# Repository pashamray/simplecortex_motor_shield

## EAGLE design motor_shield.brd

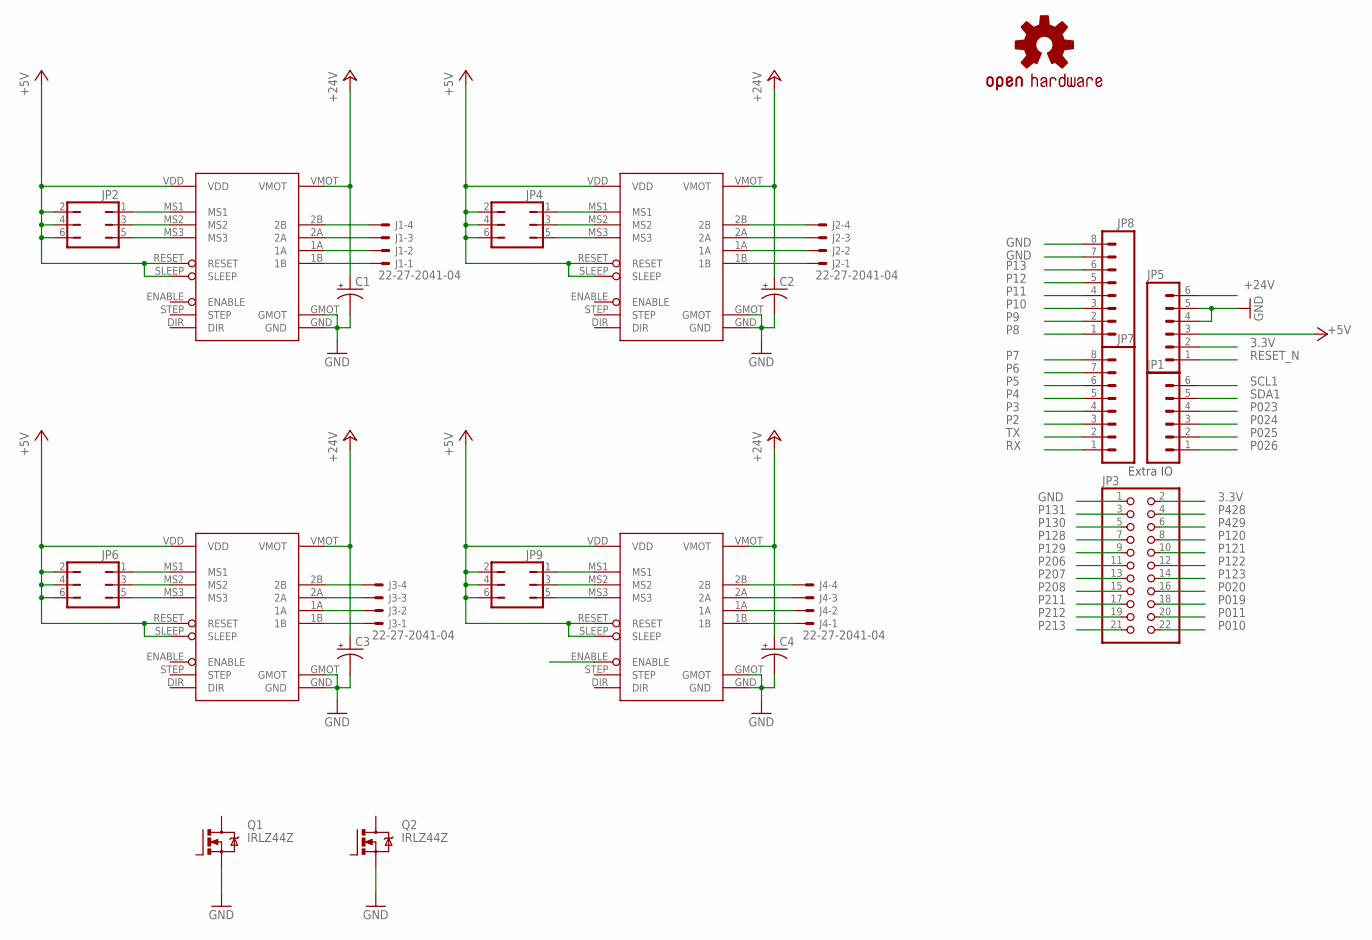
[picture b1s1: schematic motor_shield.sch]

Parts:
C1, C2, C3, C4: CAP_POLPTH1; CPOL-RADIAL-100UF-25V
J1, J2, J3, J4: 22-27-2041-04; 6410-04
JP1, JP5: M06SIP; 1X06
JP2, JP4, JP6, JP9: JP3Q
JP3: PINHD-2X11; 2X11
JP7, JP8: M08; 1X08
OPENHARDWARE: OSHW-LOGOL; OSHW-LOGO-L
Q1, Q2: IRLZ44Z; TO220BH
U$1, U$2, U$3, U$4: A4988

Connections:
3.3V: JP3.2, JP5.2
+5V: JP2.2, JP2.4, JP2.6, JP4.2, JP4.4, JP4.6, JP5.3, JP6.2, JP6.4, JP6.6, JP9.2, JP9.4, JP9.6, U$1.RESET, U$1.SLEEP, U$1.VDD, U$2.RESET, U$2.SLEEP, U$2.VDD, U$3.RESET, U$3.SLEEP, U$3.VDD, U$4.RESET, U$4.SLEEP, U$4.VDD
+24V: C1.1 (+), C2.1 (+), C3.1 (+), C4.1 (+), JP5.6, U$1.VMOT, U$2.VMOT, U$3.VMOT, U$4.VMOT
GND: C1.2 (-), C2.2 (-), C3.2 (-), C4.2 (-), JP3.1, JP5.4, JP5.5, JP8.7, JP8.8, Q1.S, Q2.S, U$1.GMOT, U$1.GND, U$2.GMOT, U$2.GND, U$3.GMOT, U$3.GND, U$4.GMOT, U$4.GND
unnamed: J1.4, U$1.2B
unnamed: J1.3, U$1.2A
unnamed: J1.2, U$1.1A
unnamed: J1.1, U$1.1B
unnamed: JP2.1, U$1.MS1
unnamed: JP2.3, U$1.MS2
unnamed: JP2.5, U$1.MS3
unnamed: J2.4, U$2.2B
unnamed: J2.3, U$2.2A
unnamed: J2.2, U$2.1A
unnamed: J2.1, U$2.1B
unnamed: JP6.1, U$3.MS1
unnamed: JP6.3, U$3.MS2
unnamed: JP6.5, U$3.MS3
unnamed: J3.4, U$3.2B
unnamed: J3.3, U$3.2A
unnamed: J3.2, U$3.1A
unnamed: J3.1, U$3.1B
unnamed: JP9.5, U$4.MS3
unnamed: JP9.3, U$4.MS2
unnamed: J4.4, U$4.2B
unnamed: J4.3, U$4.2A
unnamed: J4.2, U$4.1A
unnamed: J4.1, U$4.1B
unnamed: JP9.1, U$4.MS1
unnamed: JP4.1, U$2.MS1
unnamed: JP4.3, U$2.MS2
unnamed: JP4.5, U$2.MS3
P2: JP7.3
P3: JP7.4
P4: JP7.5
P5: JP7.6
P6: JP7.7
P7: JP7.8
P8: JP8.1
P9: JP8.2
P10: JP8.3
P010: JP3.22
P11: JP8.4
P011: JP3.20
P12: JP8.5
P13: JP8.6
P019: JP3.18
P020: JP3.16
P023: JP1.4
P024: JP1.3
P025: JP1.2
P026: JP1.1, U$4.ENABLE
P120: JP3.8
P121: JP3.10
P122: JP3.12
P123: JP3.14
P128: JP3.7
P129: JP3.9
P130: JP3.5
P131: JP3.3
P206: JP3.11
P207: JP3.13
P208: JP3.15
P211: JP3.17
P212: JP3.19
P213: JP3.21
P428: JP3.4
P429: JP3.6
RESET_N: JP5.1
RX: JP7.1
SCL1: JP1.6
SDA1: JP1.5
TX: JP7.2

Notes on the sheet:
Extra IO

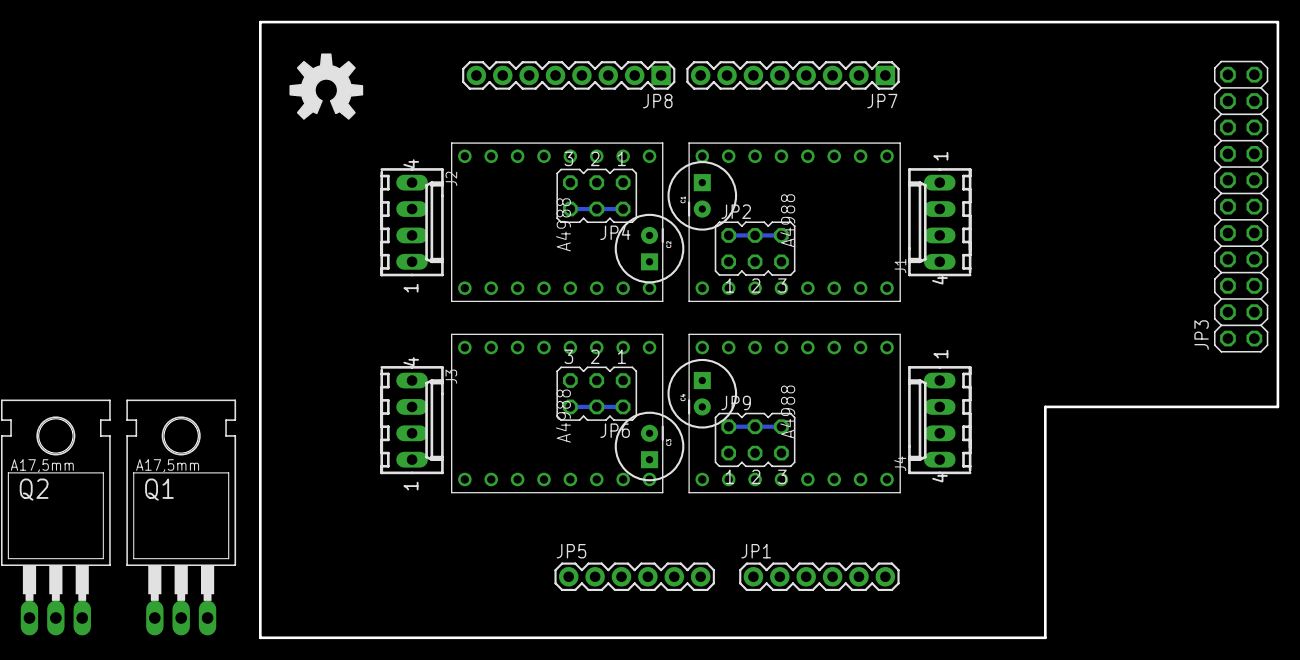
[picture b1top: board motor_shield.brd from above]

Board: 2 copper layers, 98.0 x 59.3 mm, 24 parts (0 on the bottom side), 33 nets.

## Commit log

2015-04-07 add A4988
